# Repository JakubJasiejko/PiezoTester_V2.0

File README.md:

# PiezoTester V2.0

PiezoTester V2.0 is a custom mechatronic test platform for piezoresistive and piezoelectric sensor evaluation under repeatable electromagnetic loading. The project combines an ESP32-based real-time firmware stack, a desktop control application, custom electronics, and mechanical fixtures into one reproducible research toolchain.

It is not just a “demo rig”. It is a full test bench with closed-loop load estimation, sensor-path calibration, adaptive electromagnet characterization, automated reporting, and hardware revision tracking.

## Why This Repository Matters

PiezoTester V2.0 was built to make experimental work faster, cleaner, and more defensible:

- Repeatable cyclic load generation using an electromagnet-driven actuator
- Real-time acquisition of load-cell and piezoresistive sensor data
- Calibration workflows aligned with the actual firmware implementation
- Adaptive PWM-to-load learning for feedforward-assisted ramp tests
- Standard, ramp, and hysteresis test modes
- Desktop export pipeline for CSV and PDF reports
- Versioned PCB and CAD assets kept next to the code that drives them

## Project Structure

```text
PiezoTester_V2.0/
├── firmware/         ESP32 firmware (ESP-IDF, C)
├── desktop_app/      Desktop control and reporting application (Python, PySide6)
├── hardware/
│   ├── PCB/          KiCad projects, board revisions, fabrication outputs
│   └── CAD/          Mechanical CAD parts and assemblies
├── sample_results/   Example CSV/PDF outputs generated by the system
├── docs/             Cross-project documentation, asset sources, image placeholders
├── LICENSE
└── README.md
```

## Core Features

- Multi-mode testing: standard, ramp, and hysteresis acquisition
- One-point load-cell calibration with nominal model correction
- Sensor-path resistance calibration using a reference resistor
- Continuous live mass preview in the calibration workflow
- Advanced electromagnet contact calibration with stored contact-state tables
- Learned PWM-to-load map with point insertion, sorting, interpolation, and reuse
- Feedforward-assisted ramp control with bounded correction steps
- Automatic test summary generation with CSV/PDF export support
- Hardware revision history covering PCB and mechanical development

## Technical Highlights

- Nominal load-cell model based on beam capacity, sensitivity, excitation voltage, and analog gain
- Absolute-value load signal handling to avoid negative mass artifacts
- Resistance reconstruction from divider voltage with a calibration factor stored in NVS
- Electromagnet premodel derived from movement/contact thresholds
- Learned actuator model stored as empirical `(PWM, mass)` pairs
- Piecewise-linear feedforward estimate for ramp tests
- Iterative predictive-corrective update in the ramp controller
- Burst acquisition for hysteresis traces at high sample rate

## Recent Project Wins

- A research-grade calibration flow that mirrors the actual firmware math
- On-device learning of electromagnet behavior instead of fixed lookup-only control
- Integrated desktop reporting that produces presentation-ready PDF summaries
- Multiple PCB revisions with local symbol, footprint, and 3D asset preservation
- A repository structure now being shaped to support publication, fabrication, and onboarding

## Visuals

Add your best visuals here and the repository will immediately look much more “product-level”.

### Hero Shot

_Suggested image: full assembled device on bench, powered on, with the desktop UI visible in the background._

### Desktop Application

_Suggested image: the main control window with charts, statistics, and connection status._

### PCB Render

_Suggested image: 3D render of the latest board revision in KiCad._

### Mechanical Assembly

_Suggested image: CAD assembly or the real fixture with the load cell, electromagnet, and specimen stage._

## Getting Started

### Firmware

See [firmware/README.md](firmware/README.md) for build, flash, and architecture details.

### Desktop Application

See [desktop_app/README.md](desktop_app/README.md) for runtime requirements, launch instructions, and export workflow notes.

### Hardware

See:

- [hardware/README.md](hardware/README.md)
- [hardware/PCB/README.md](hardware/PCB/README.md)
- [hardware/CAD/README.md](hardware/CAD/README.md)

## Asset Sources and Dependencies

The repository intentionally keeps third-party footprint/model provenance visible instead of burying it in tool-generated files.

See:

- [docs/README.md](docs/README.md)
- [docs/THIRD_PARTY_SOURCES.md](docs/THIRD_PARTY_SOURCES.md)

## Sample Outputs

Representative test artifacts are stored in [sample_results/README.md](sample_results/README.md).

## Self-Praise, Because It Is Earned

This project is a serious piece of interdisciplinary work:

- Embedded systems
- measurement engineering
- mechatronic actuation
- hardware design
- desktop tooling
- experimental workflow design

That combination is hard to execute well, and PiezoTester V2.0 already shows a lot more systems thinking than a typical “lab side-project”. It deserves to look the part.

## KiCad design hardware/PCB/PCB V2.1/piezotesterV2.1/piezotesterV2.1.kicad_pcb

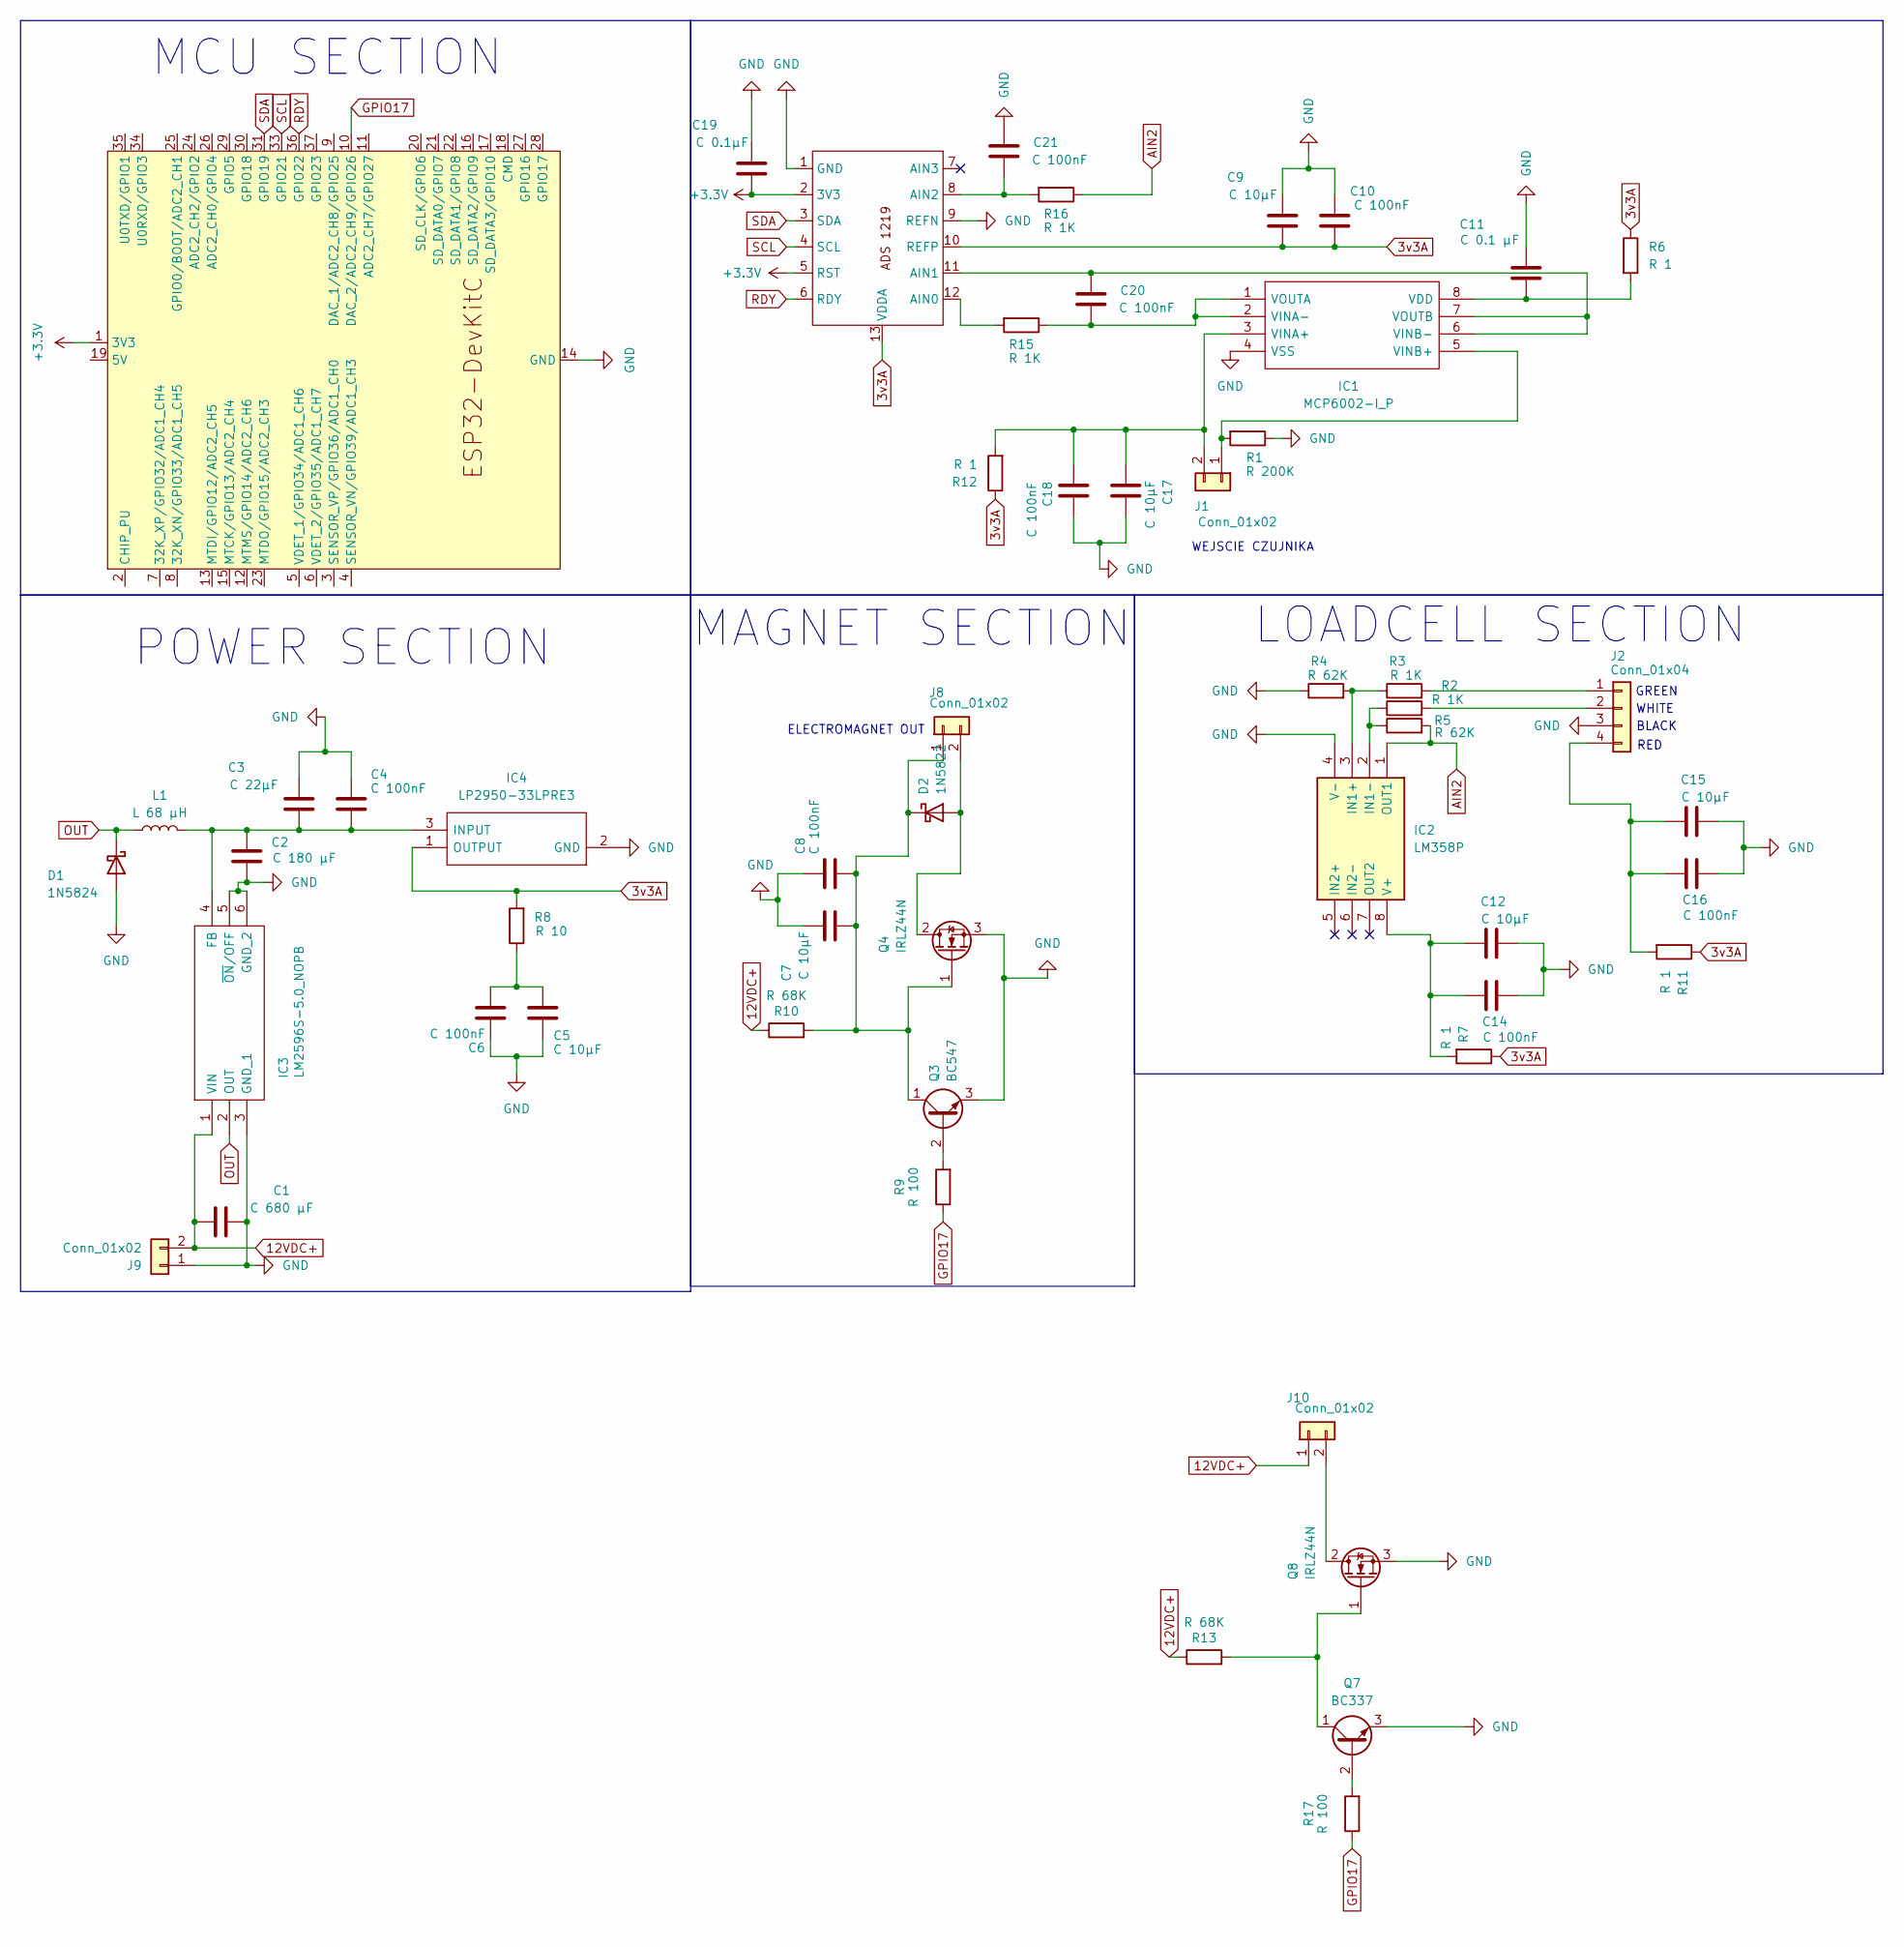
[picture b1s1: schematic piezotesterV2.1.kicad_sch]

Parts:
ADS2: ADS1219
C1: C 680 μF; CP_Radial_D10.0mm_P5.00mm
C2: C 180 μF; CP_Radial_D8.0mm_P3.50mm
C3: C 22μF; C_1206_3216Metric
C4, C6, C8, C10, C14, C16, C18, C20, C21: C 100nF; C_1206_3216Metric
C5, C7, C9, C12, C15, C17: C 10μF; C_1206_3216Metric
C11: C 0.1 μF; C_1206_3216Metric
C19: C 0.1μF; C_1206_3216Metric
D1: 1N5824; D_DO-201AD_P15.24mm_Horizontal
D2: 1N5822; D_DO-201AD_P15.24mm_Horizontal
IC1: MCP6002-I_P; DIP781W56P254L950H533Q8N; Mouser Part Number 579-MCP6002-I/P
IC2: LM358P; DIP781W56P254L950H533Q8N; Mouser Part Number 595-LM358P
IC3: LM2596S-5.0_NOPB; KTT0005B; Mouser Part Number 926-LM2596S-5.0/NOPB
IC4: LP2950-33LPRE3; TL431CLPM; Mouser Part Number 595-LP2950-33LPRE3
J1, J8, J9, J10: Conn_01x02; PinHeader_1x02_P2.54mm_Horizontal
J2: Conn_01x04; PinHeader_1x04_P2.54mm_Horizontal
L1: L 68 μH; L_12x12mm_H6mm
Q3: BC547; TO-92_Inline
Q4, Q8: IRLZ44N; TO-220-3_Vertical
Q7: BC337; TO-92_Inline
R1: R 200K; R_1206_3216Metric
R2, R3, R15, R16: R 1K; R_1206_3216Metric
R4, R5: R 62K; R_1206_3216Metric
R6, R7, R11, R12: R 1; R_1206_3216Metric
R8: R 10; R_1206_3216Metric
R9, R17: R 100; R_1206_3216Metric
R10, R13: R 68K; R_1206_3216Metric
U1: ESP32-DevKitC

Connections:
3v3A: ADS2.10 (REFP), ADS2.13 (VDDA), C9.1, C10.1, IC4.1 (OUTPUT), R6.1, R7.1, R8.2, R11.1, R12.1
12VDC+: C1.1, IC3.1 (VIN), J9.2, J10.1, R10.1, R13.1
+3.3V: ADS2.2 (3V3), ADS2.5 (RST), C19.1, U1.1 (3V3)
AIN2: IC2.1 (OUT1), R5.2, R16.1
GND: ADS2.1 (GND), ADS2.9 (REFN), C1.2, C2.1, C3.2, C4.2, C5.2, C6.2, C7.2, C8.2, C9.2, C10.2, C11.2, C12.2, C14.2, C15.2, C16.2, C17.2, C18.2, C19.2, C21.2, D1.2 (A), IC1.4 (VSS), IC2.4 (V-), IC3.3 (GND_1), IC3.5 (~ON/OFF), IC3.6 (GND_2), IC4.2 (GND), J2.3, J9.1, Q3.3 (E), Q4.3 (S), Q7.3 (E), Q8.3 (S), R1.1, R4.1, U1.14 (GND), U1.32 (GND), U1.38 (GND)
GPIO17: R9.1, R17.1, U1.10 (DAC_2/ADC2_CH9/GPIO26)
unnamed: ADS2.12 (AIN0), R15.2
unnamed: ADS2.11 (AIN1), C20.2, IC1.6 (VINB-), IC1.7 (VOUTB)
unnamed: ADS2.8 (AIN2), C21.1, R16.2
unnamed: C5.1, C6.1, R8.1
unnamed: D2.2 (A), J8.2, Q4.2 (D)
unnamed: C7.1, C8.1, D2.1 (K), J8.1, Q3.1 (C), Q4.1 (G), R10.2
unnamed: C11.1, IC1.8 (VDD), R6.2
unnamed: C17.1, C18.1, IC1.3 (VINA+), J1.2, R12.2
unnamed: C20.1, IC1.1 (VOUTA), IC1.2 (VINA-), R15.1
unnamed: IC1.5 (VINB+), J1.1, R1.2
unnamed: IC2.3 (IN1+), R3.1, R4.2
unnamed: IC2.2 (IN1-), R2.1, R5.1
unnamed: C12.1, C14.1, IC2.8 (V+), R7.2
unnamed: C2.2, C3.1, C4.1, IC3.4 (FB), IC4.3 (INPUT), L1.2
unnamed: J2.1, R3.2
unnamed: J2.2, R2.2
unnamed: C15.1, C16.1, J2.4, R11.2
unnamed: J10.2, Q8.2 (D)
unnamed: Q3.2 (B), R9.2
unnamed: Q7.1 (C), Q8.1 (G), R13.2
unnamed: Q7.2 (B), R17.2
OUT: D1.1 (K), IC3.2 (OUT), L1.1
RDY: ADS2.6 (RDY), U1.36 (GPIO22)
SCL: ADS2.4 (SCL), U1.33 (GPIO21)
SDA: ADS2.3 (SDA), U1.31 (GPIO19)

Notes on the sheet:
ELECTROMAGNET OUT
WHITE
MCU SECTION
BLACK
POWER SECTION
RED
WEJSCIE CZUJNIKA
MAGNET SECTION
GREEN
LOADCELL SECTION

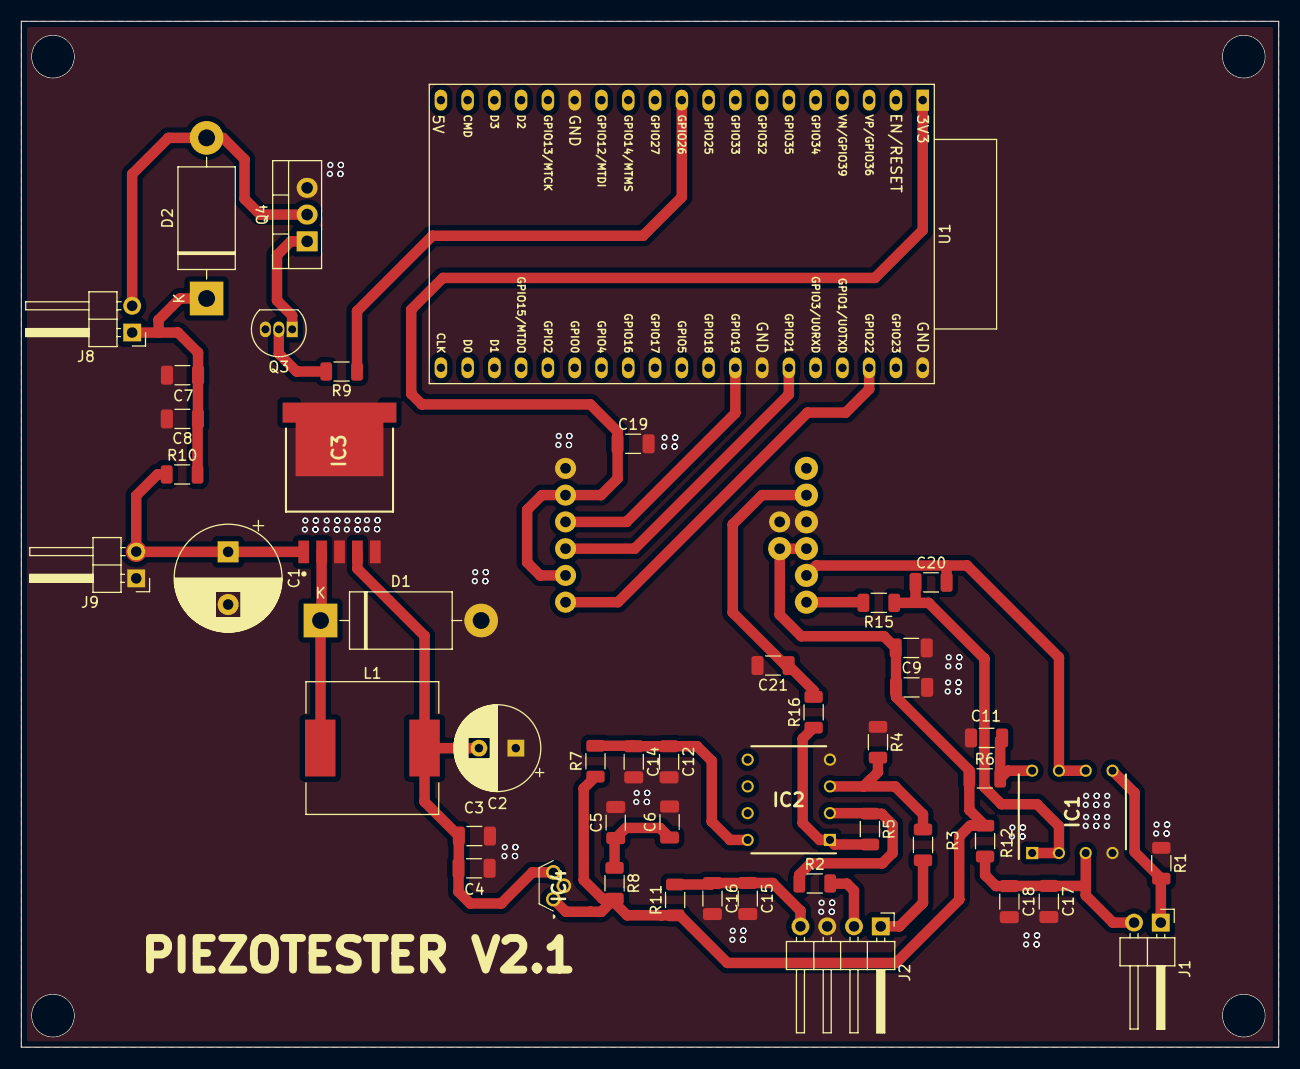
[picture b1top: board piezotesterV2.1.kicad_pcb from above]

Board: 2 copper layers, 119.3 x 97.3 mm, 49 parts (0 on the bottom side), 28 nets.

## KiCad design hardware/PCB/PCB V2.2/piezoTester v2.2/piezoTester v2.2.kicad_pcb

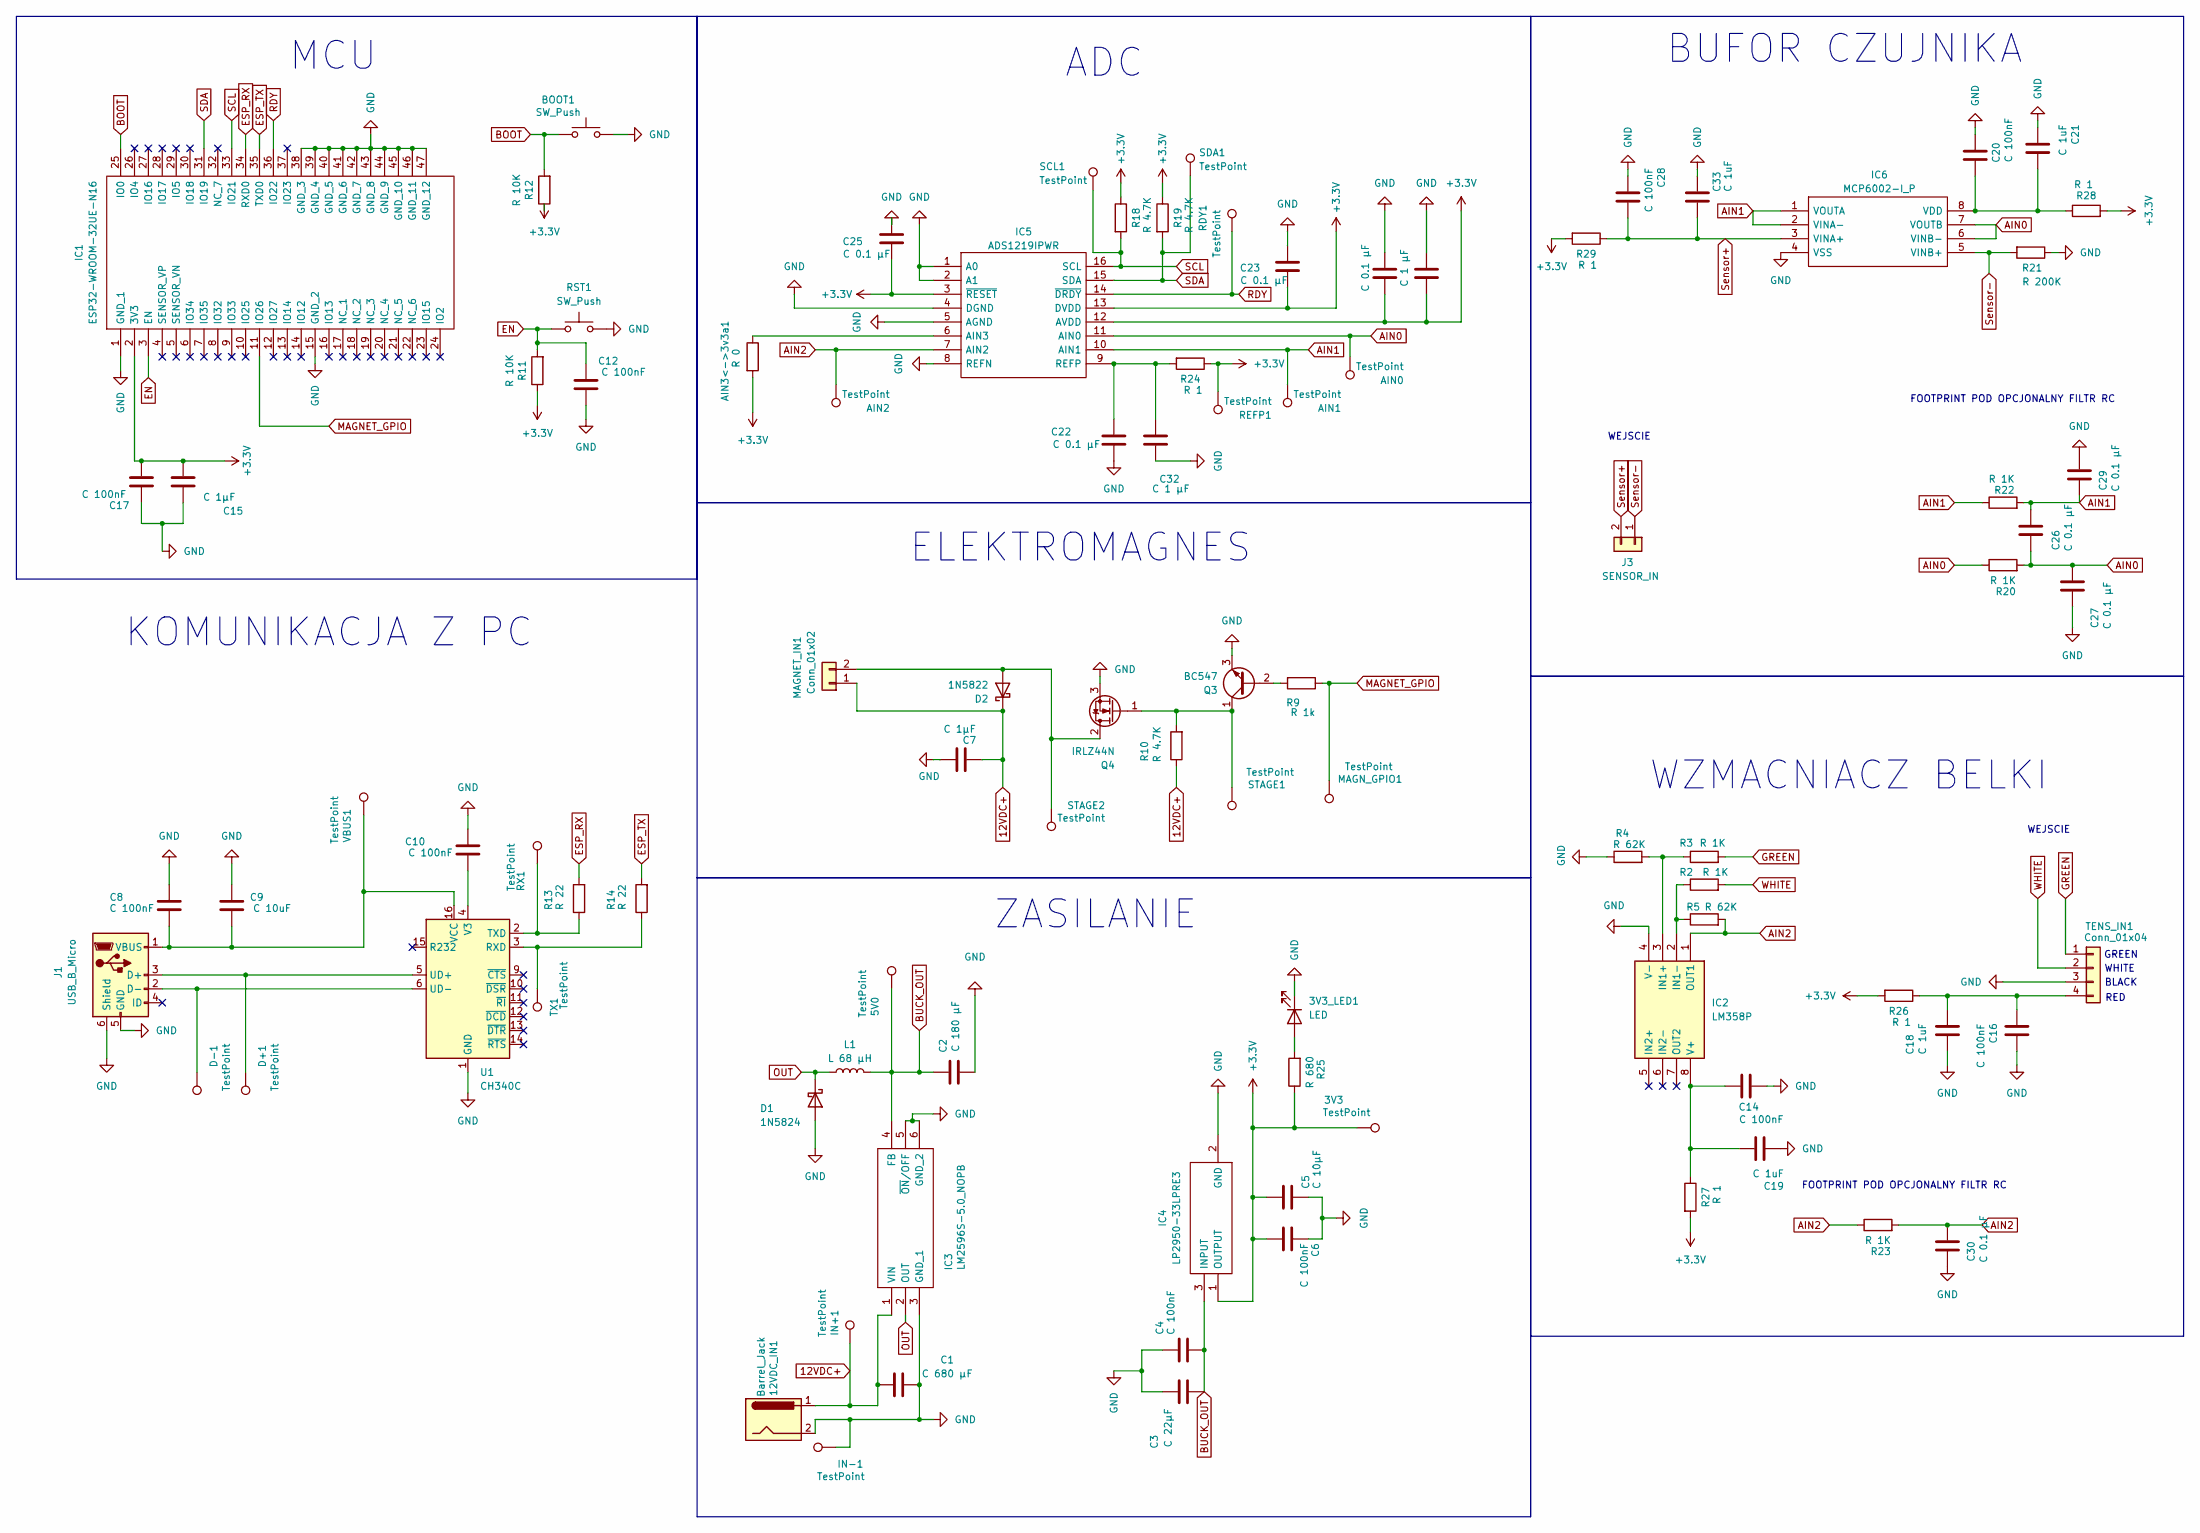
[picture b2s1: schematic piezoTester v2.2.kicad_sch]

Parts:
3V3, 5V0: TestPoint; TestPoint_Pad_D1.0mm
3V3_LED1: LED; LED_1206_3216Metric_Pad1.42x1.75mm_HandSolder
12VDC_IN1: Barrel_Jack; BarrelJack_Wuerth_694108106102_2.5x5.5mm
AIN0, AIN1, AIN2: TestPoint; TestPoint_Pad_D1.0mm
AIN3<->3v3a1: R 0; R_0603_1608Metric_Pad0.98x0.95mm_HandSolder
BOOT1: SW_Push; SW_PUSH_6mm
C1: C 680 μF; CP_Radial_D10.0mm_P5.00mm
C2: C 180 μF; CP_Radial_D8.0mm_P3.50mm
C3: C 22μF; C_1206_3216Metric_Pad1.33x1.80mm_HandSolder
C4, C6, C10, C12, C28: C 100nF; C_1206_3216Metric_Pad1.33x1.80mm_HandSolder
C5: C 10μF; C_1206_3216Metric_Pad1.33x1.80mm_HandSolder
C7: C 1μF; C_1206_3216Metric_Pad1.33x1.80mm_HandSolder
C8, C14, C16, C17, C20: C 100nF; C_0603_1608Metric_Pad1.08x0.95mm_HandSolder
C9: C 10uF; C_0603_1608Metric_Pad1.08x0.95mm_HandSolder
C15: C 1μF; C_0603_1608Metric_Pad1.08x0.95mm_HandSolder
C18, C19, C21: C 1uF; C_0603_1608Metric_Pad1.08x0.95mm_HandSolder
C22, C23, C24, C25, C26: C 0.1 μF; C_0603_1608Metric_Pad1.08x0.95mm_HandSolder
C27, C29, C30: C 0.1 μF; C_1206_3216Metric_Pad1.33x1.80mm_HandSolder
C31, C32: C 1 μF; C_0603_1608Metric_Pad1.08x0.95mm_HandSolder
C33: C 1uF; C_1206_3216Metric_Pad1.33x1.80mm_HandSolder
D1: 1N5824; D_DO-201AD_P15.24mm_Horizontal
D2: 1N5822; D_DO-201AD_P15.24mm_Horizontal
D+1: TestPoint; TestPoint_Pad_D1.0mm
D-1: TestPoint; TestPoint_Pad_D1.0mm
IC1: ESP32-WROOM-32UE-N16; ESP32WROOM32UEN16; Manufacturer_Part_Number ESP32-WROOM-32UE-N16
IC2: LM358P; DIP781W56P254L950H533Q8N; Mouser Part Number 595-LM358P
IC3: LM2596S-5.0_NOPB; KTT0005B; Mouser Part Number 926-LM2596S-5.0/NOPB
IC4: LP2950-33LPRE3; TL431CLPM; Mouser Part Number 595-LP2950-33LPRE3
IC5: ADS1219IPWR; ads1219; Mouser Part Number 595-ADS1219IPWR
IC6: MCP6002-I_P; DIP781W56P254L950H533Q8N; Mouser Part Number 579-MCP6002-I/P
IN+1: TestPoint; TestPoint_Pad_D1.0mm
IN-1: TestPoint; TestPoint_Pad_D1.0mm
J1: USB_B_Micro; USB_Micro-B_Wuerth_629105150521
J3: SENSOR_IN; PinHeader_1x02_P2.54mm_Vertical
L1: L 68 μH; L_12x12mm_H6mm
MAGNET_IN1: Conn_01x02; PinHeader_1x02_P2.54mm_Vertical
MAGN_GPIO1: TestPoint; TestPoint_Pad_D1.0mm
Q3: BC547; TO-92_Inline
Q4: IRLZ44N; TO-220-3_Horizontal_TabDown
R2, R3, R20, R22, R23: R 1K; R_1206_3216Metric_Pad1.30x1.75mm_HandSolder
R4, R5: R 62K; R_1206_3216Metric_Pad1.30x1.75mm_HandSolder
R9: R 1k; R_1206_3216Metric_Pad1.30x1.75mm_HandSolder
R10: R 4.7K; R_1206_3216Metric_Pad1.30x1.75mm_HandSolder
R11, R12: R 10K; R_1206_3216Metric_Pad1.30x1.75mm_HandSolder
R13, R14: R 22; R_1206_3216Metric_Pad1.30x1.75mm_HandSolder
R18, R19: R 4.7K; R_0603_1608Metric_Pad0.98x0.95mm_HandSolder
R21: R 200K; R_1206_3216Metric_Pad1.30x1.75mm_HandSolder
R24: R 1; R_0603_1608Metric_Pad0.98x0.95mm_HandSolder
R25: R 680; R_1206_3216Metric_Pad1.30x1.75mm_HandSolder
R26, R27, R28, R29: R 1; R_1206_3216Metric_Pad1.30x1.75mm_HandSolder
RDY1: TestPoint; TestPoint_Pad_D1.0mm
REFP1: TestPoint; TestPoint_Pad_D1.0mm
RST1: SW_Push; SW_PUSH_6mm
RX1: TestPoint; TestPoint_Pad_D1.0mm
SCL1: TestPoint; TestPoint_Pad_D1.0mm
SDA1: TestPoint; TestPoint_Pad_D1.0mm
STAGE1, STAGE2: TestPoint; TestPoint_Pad_D1.0mm
TENS_IN1: Conn_01x04; PinHeader_1x04_P2.54mm_Vertical
TX1: TestPoint; TestPoint_Pad_D1.0mm
U1: CH340C; SOIC-16_3.9x9.9mm_P1.27mm
VBUS1: TestPoint; TestPoint_Pad_D1.0mm

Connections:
12VDC+: 12VDC_IN1.1, C1.1, C7.2, D2.1 (K), IC3.1 (VIN), IN+1.1, MAGNET_IN1.1, R10.1
+3.3V: 3V3.1, AIN3<->3v3a1.2, C5.1, C6.1, C15.1, C17.1, C23.1, C24.1, C25.1, C31.1, IC1.2 (3V3), IC4.1 (OUTPUT), IC5.3 (~RESET), IC5.12 (AVDD), IC5.13 (DVDD), R11.1, R12.1, R18.1, R19.1, R24.1, R25.1, R26.2, R27.2, R28.2, R29.2, REFP1.1; also elsewhere on the board
AIN0: AIN0.1, C26.2, C27.1, IC5.11 (AIN0), IC6.6 (VINB-), IC6.7 (VOUTB), R20.1, R20.2; also elsewhere on the board
AIN1: AIN1.1, C26.1, C29.2, IC5.10 (AIN1), IC6.1 (VOUTA), IC6.2 (VINA-), R22.1, R22.2; also elsewhere on the board
AIN2: AIN2.1, C30.1, IC2.1 (OUT1), IC5.7 (AIN2), R5.2, R23.1, R23.2; also elsewhere on the board
BOOT: BOOT1.1, IC1.25 (IO0), R12.2; also elsewhere on the board
BUCK_OUT: 5V0.1, C2.2, C3.1, C4.1, IC3.4 (FB), IC4.3 (INPUT), L1.2; also elsewhere on the board
EN: C12.2, IC1.3 (EN), R11.2, RST1.1; also elsewhere on the board
ESP_RX: IC1.34 (RXD0), R13.2; also elsewhere on the board
ESP_TX: IC1.35 (TXD0), R14.2; also elsewhere on the board
GND: 3V3_LED1.1 (K), 12VDC_IN1.2, BOOT1.2, C1.2, C2.1, C3.2, C4.2, C5.2, C6.2, C7.1, C8.2, C9.2, C10.2, C12.1, C14.2, C15.2, C16.2, C17.2, C18.2, C19.2, C20.2, C21.2, C22.1, C23.2, C24.2, C25.2, C27.2, C28.2, C29.1, C30.2, C31.2, C32.1, C33.1, D1.2 (A), IC1.1 (GND_1), IC1.15 (GND_2), IC1.38 (GND_3), IC1.39 (GND_4), IC1.40 (GND_5), IC1.41 (GND_6), IC1.42 (GND_7), IC1.43 (GND_8), IC1.44 (GND_9), IC1.45 (GND_10), IC1.46 (GND_11), IC1.47 (GND_12), IC2.4 (V-), IC3.3 (GND_1), IC3.5 (~ON/OFF), IC3.6 (GND_2), IC3.7, IC3.8, IC4.2 (GND), IC5.1 (A0), IC5.2 (A1), IC5.4 (DGND), IC5.5 (AGND), IC5.8 (REFN), IC6.4 (VSS), IN-1.1, J1.5 (GND), J1.6 (Shield), Q3.3 (E), Q4.3 (S), R4.1, R21.1, RST1.2, TENS_IN1.3, U1.1 (GND); also elsewhere on the board
GREEN: R3.2, TENS_IN1.1
MAGNET_GPIO: IC1.11 (IO26), MAGN_GPIO1.1, R9.1; also elsewhere on the board
unnamed: 3V3_LED1.2 (A), R25.2
unnamed: D2.2 (A), MAGNET_IN1.2, Q4.2 (D), STAGE2.1
unnamed 15: IC2.3 (IN1+), R3.1, R4.2; also elsewhere on the board
unnamed 16: IC2.2 (IN1-), R2.1, R5.1; also elsewhere on the board
unnamed 17: C14.1, C19.1, IC2.8 (V+), R27.1; also elsewhere on the board
unnamed 18: AIN3<->3v3a1.1, IC5.6 (AIN3); also elsewhere on the board
unnamed: C22.2, C32.2, IC5.9 (REFP), R24.2
unnamed 20: C20.1, C21.1, IC6.8 (VDD), R28.1; also elsewhere on the board
unnamed: D+1.1, J1.3 (D+), U1.5 (UD+)
unnamed: D-1.1, J1.2 (D-), U1.6 (UD-)
unnamed: C8.1, C9.1, J1.1 (VBUS), U1.16 (VCC), VBUS1.1
unnamed: Q3.2 (B), R9.2
unnamed: Q3.1 (C), Q4.1 (G), R10.2, STAGE1.1
unnamed: C16.1, C18.1, R26.1, TENS_IN1.4
unnamed: R14.1, TX1.1, U1.3 (RXD)
unnamed: R13.1, RX1.1, U1.2 (TXD)
unnamed: C10.1, U1.4 (V3)
OUT: D1.1 (K), IC3.2 (OUT), L1.1
RDY: IC1.36 (IO22), IC5.14 (~DRDY), RDY1.1; also elsewhere on the board
SCL: IC1.33 (IO21), IC5.16 (SCL), R18.2, SCL1.1; also elsewhere on the board
SDA: IC1.31 (IO19), IC5.15 (SDA), R19.2, SDA1.1; also elsewhere on the board
Sensor+: C28.1, C33.2, IC6.3 (VINA+), J3.2, R29.1; also elsewhere on the board
Sensor-: IC6.5 (VINB+), J3.1, R21.2; also elsewhere on the board
WHITE: R2.2, TENS_IN1.2

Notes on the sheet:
WEJSCIE
FOOTPRINT POD OPCJONALNY FILTR RC
WHITE
BLACK
BUFOR CZUJNIKA
KOMUNIKACJA Z PC
ZASILANIE
RED
MCU
ELEKTROMAGNES
GREEN
ADC
WZMACNIACZ BELKI

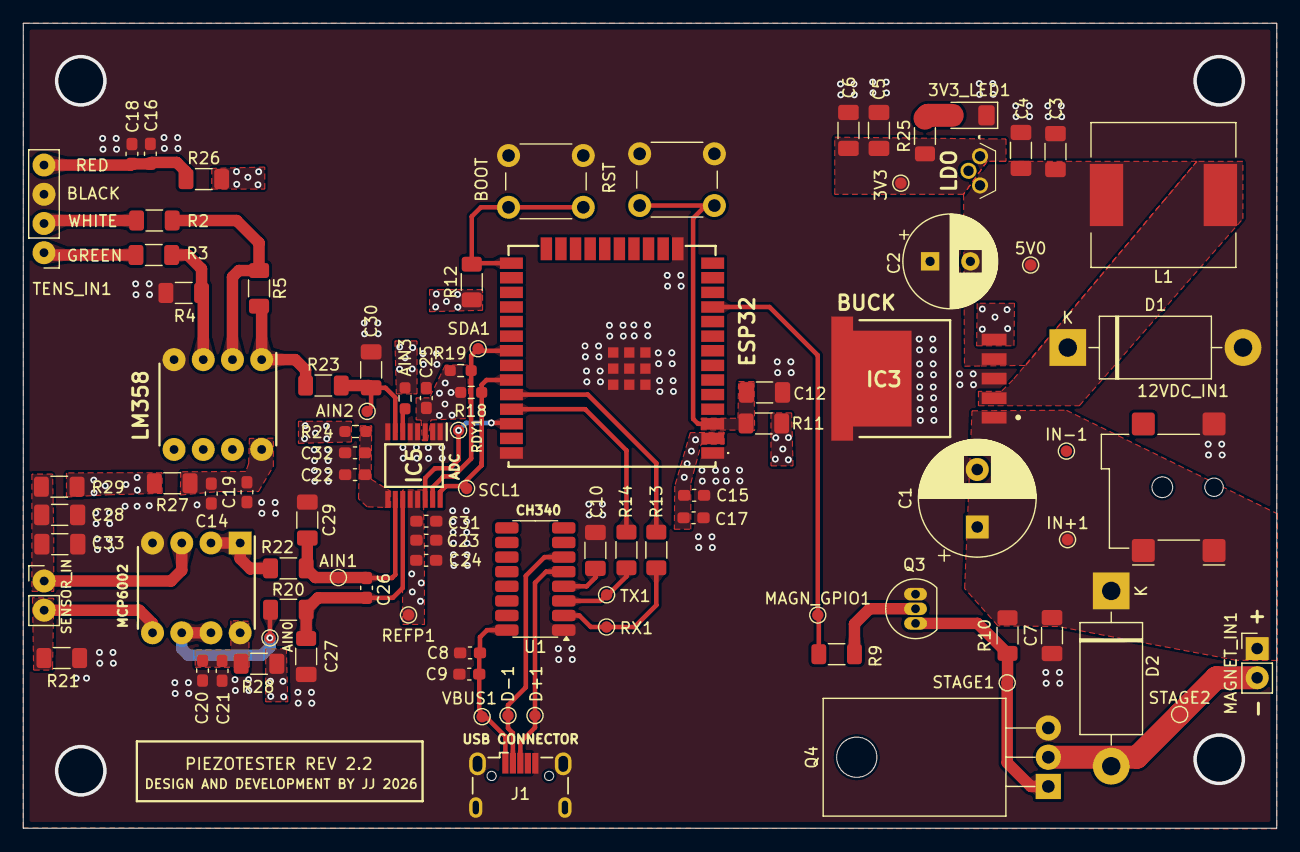
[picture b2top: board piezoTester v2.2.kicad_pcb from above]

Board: 4 copper layers, 109.0 x 70.0 mm, 93 parts (0 on the bottom side), 37 nets.

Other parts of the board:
AIN3: R 0; R_0603_1608Metric_Pad0.98x0.95mm_HandSolder
BOOT: SW_Push; SW_PUSH_6mm
ESP32: ESP32-WROOM-32UE-N16; ESP32WROOM32UEN16
LDO: LP2950-33LPRE3; TL431CLPM
LM358: LM358P; DIP781W56P254L950H533Q8N
MCP6002: MCP6002-I_P; DIP781W56P254L950H533Q8N
RST: SW_Push; SW_PUSH_6mm
SENSOR_IN: SENSOR_IN; PinHeader_1x02_P2.54mm_Vertical

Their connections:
+3.3V: AIN3.2, ESP32.2 (3V3), LDO.1 (OUTPUT); also elsewhere on the board
AIN0: MCP6002.6 (VINB-), MCP6002.7 (VOUTB); also elsewhere on the board
AIN1: MCP6002.1 (VOUTA), MCP6002.2 (VINA-); also elsewhere on the board
AIN2: LM358.1 (OUT1); also elsewhere on the board
BOOT: BOOT.1, ESP32.25 (IO0); also elsewhere on the board
BUCK_OUT: LDO.3 (INPUT); also elsewhere on the board
EN: ESP32.3 (EN), RST.1; also elsewhere on the board
ESP_RX: ESP32.34 (RXD0); also elsewhere on the board
ESP_TX: ESP32.35 (TXD0); also elsewhere on the board
GND: BOOT.2, ESP32.1 (GND_1), ESP32.15 (GND_2), ESP32.38 (GND_3), ESP32.39 (GND_4), ESP32.40 (GND_5), ESP32.41 (GND_6), ESP32.42 (GND_7), ESP32.43 (GND_8), ESP32.44 (GND_9), ESP32.45 (GND_10), ESP32.46 (GND_11), ESP32.47 (GND_12), LDO.2 (GND), LM358.4 (V-), MCP6002.4 (VSS), RST.2; also elsewhere on the board
MAGNET_GPIO: ESP32.11 (IO26); also elsewhere on the board
unnamed 15: LM358.3 (IN1+); also elsewhere on the board
unnamed 16: LM358.2 (IN1-); also elsewhere on the board
unnamed 17: LM358.8 (V+); also elsewhere on the board
unnamed 18: AIN3.1; also elsewhere on the board
unnamed 20: MCP6002.8 (VDD); also elsewhere on the board
RDY: ESP32.36 (IO22); also elsewhere on the board
SCL: ESP32.33 (IO21); also elsewhere on the board
SDA: ESP32.31 (IO19); also elsewhere on the board
Sensor+: MCP6002.3 (VINA+), SENSOR_IN.2; also elsewhere on the board
Sensor-: MCP6002.5 (VINB+), SENSOR_IN.1; also elsewhere on the board

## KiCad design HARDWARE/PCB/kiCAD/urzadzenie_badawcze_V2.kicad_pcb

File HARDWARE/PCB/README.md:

# PCB

This directory stores the electrical design history of PiezoTester V2.0 in KiCad.

## Available Revisions

- `PCB V2.0`
  Early board revision and legacy project assets.
- `PCB V2.1`
  Intermediate revision with local 3D model integration.
- `PCB V2.2`
  Later revision with fabrication outputs and local symbol / footprint libraries.

## What You Will Find Here

- `.kicad_pro`, `.kicad_sch`, `.kicad_pcb` source files
- Local symbol and footprint libraries
- Local 3D models used by KiCad
- Gerber exports and production artifacts
- Revision-specific backup archives generated by KiCad

## Source Provenance

This repository mixes:

- custom project-specific KiCad symbols and footprints
- vendor-derived assets from SamacSys-style libraries
- SparkFun and Espressif-derived reference models for selected modules
- local fixes applied so 3D models resolve directly from the repository

See [../../docs/THIRD_PARTY_SOURCES.md](../../docs/THIRD_PARTY_SOURCES.md) for the documented origin of the main assets.

## Practical Note

KiCad creates autosaves, lock files, cache files, and backups aggressively during active design sessions. The repository now documents these artifacts explicitly and ignores the transient ones where possible, while preserving revision history that is actually useful.

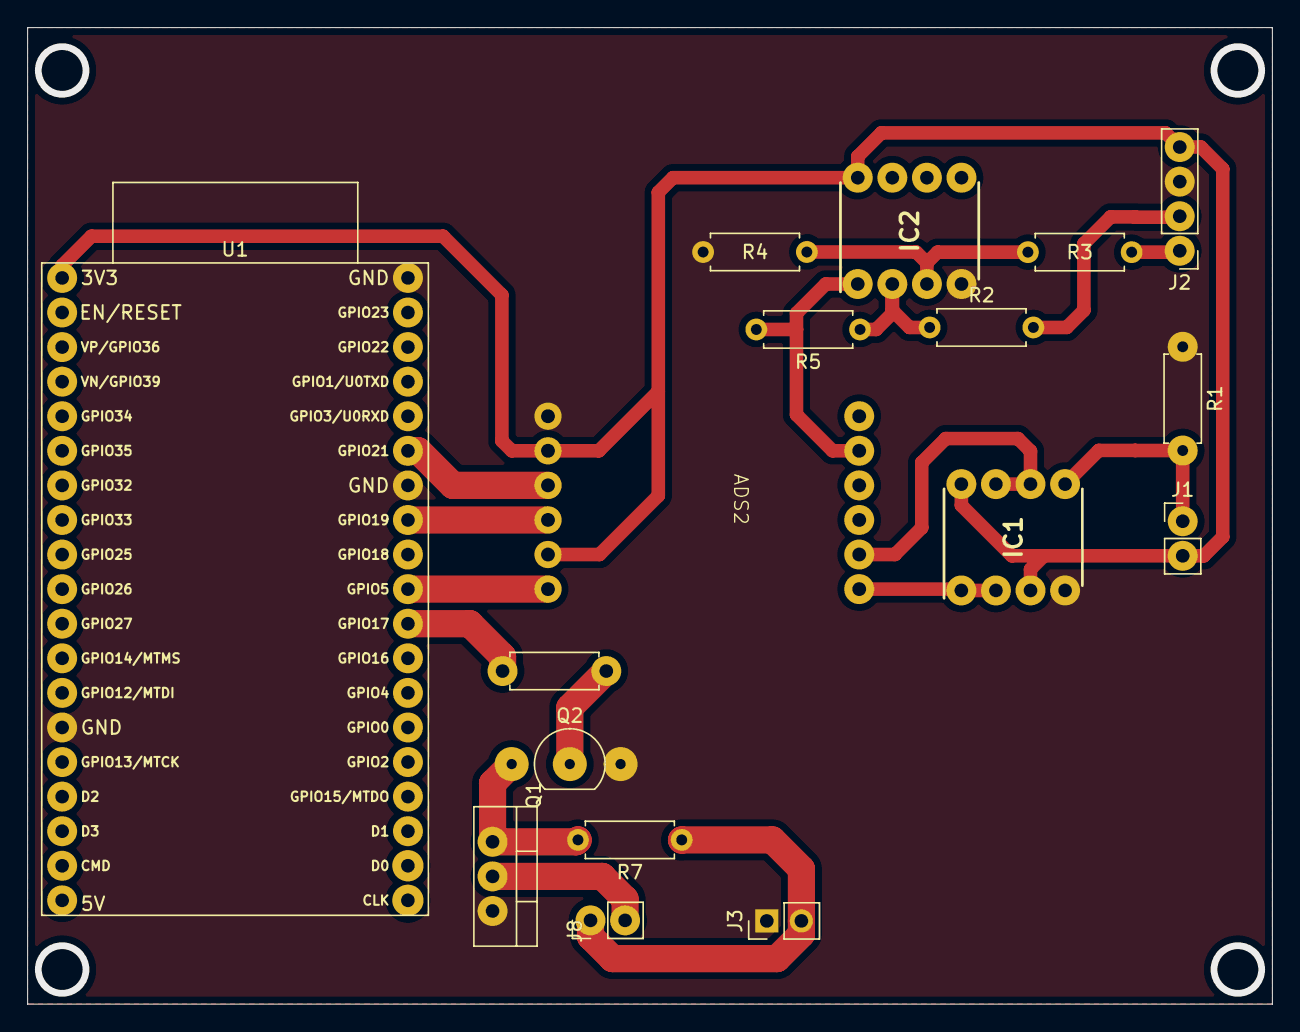
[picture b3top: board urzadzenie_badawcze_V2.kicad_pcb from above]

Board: 2 copper layers, 91.4 x 71.7 mm, 17 parts (0 on the bottom side), 18 nets.

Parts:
ADS2: ADS1219
IC1: MCP6002-I_P; DIP781W56P254L950H533Q8N
IC2: LM358P; DIP781W56P254L950H533Q8N
J1, J3, J8: Conn_01x02; PinHeader_1x02_P2.54mm_Vertical
J2: Conn_01x04; PinHeader_1x04_P2.54mm_Vertical
Q1: IRLZ44N; TO-220-3_Vertical
Q2: BC547; TO-92_Inline
R1: R 200K; R_Axial_DIN0207_L6.3mm_D2.5mm_P7.62mm_Horizontal
R2, R3: R 1K; R_Axial_DIN0207_L6.3mm_D2.5mm_P7.62mm_Horizontal
R4, R5: R 62K; R_Axial_DIN0207_L6.3mm_D2.5mm_P7.62mm_Horizontal
R6: R 100; R_Axial_DIN0207_L6.3mm_D2.5mm_P7.62mm_Horizontal
R7: R 68K; R_Axial_DIN0207_L6.3mm_D2.5mm_P7.62mm_Horizontal
U1: ESP32-DevKitC

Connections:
+3.3V: ADS2.2 (3V3), ADS2.5 (RST), IC1.3 (VINA+), IC1.8 (VDD), IC2.8 (V+), J1.2, J2.4, U1.1 (3V3)
GND: ADS2.1 (GND), IC1.4 (VSS), IC2.4 (V-), J2.3, J3.1, Q1.3 (S), Q2.3 (E), R1.1, R4.1, U1.14 (GND), U1.32 (GND), U1.38 (GND)
GPIO17: R6.1, U1.28 (GPIO17)
unnamed: ADS2.12 (AIN0), IC1.1 (VOUTA), IC1.2 (VINA-)
unnamed: ADS2.11 (AIN1), IC1.6 (VINB-), IC1.7 (VOUTB)
unnamed: ADS2.8 (AIN2), IC2.1 (OUT1), R5.2
unnamed: IC1.5 (VINB+), J1.1, R1.2
unnamed: IC2.3 (IN1+), R3.1, R4.2
unnamed: IC2.2 (IN1-), R2.1, R5.1
unnamed: J2.1, R3.2
unnamed: J2.2, R2.2
unnamed: J3.2, J8.1, R7.1
unnamed: J8.2, Q1.2 (D)
unnamed: Q1.1 (G), Q2.1 (C), R7.2
unnamed: Q2.2 (B), R6.2
RDY: ADS2.6 (RDY), U1.29 (GPIO5)
SCL: ADS2.4 (SCL), U1.31 (GPIO19)
SDA: ADS2.3 (SDA), U1.33 (GPIO21)

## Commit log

2025-11-10 Added Matlab and PCB V2.1 completed fw
2026-03-14 PCB v2.2
2026-04-17 feat: add nominal load-cell calibration flow
2026-04-17 fix: auto-start live preview and harden pdf export
2026-04-18 feat: add ramp test mode with pwm learning
2026-04-18 feat: add electromagnet premodel controls
2026-04-18 feat: split electromagnet movement and contact thresholds
2026-04-18 feat: add advanced electromagnet calibration tools
2026-04-18 fix: suspend live preview during zero calibration
2026-04-18 refactor: simplify calibration flow and speed preview
2026-04-18 fix: stabilize calibration dialog startup
2026-04-18 fix: avoid GUI updates from calibration worker threads
2026-04-18 fix: open summary dialog after automatic test completion
2026-04-18 feat: add point-by-point electromagnet contact calibration table
2026-04-18 feat: persist electromagnet contact calibration points
2026-04-18 refactor: make contact calibration grid configurable
2026-04-18 ux: prefer ttyUSB ports in selector
2026-04-18 fix: preserve selected contact state during config sync
2026-04-18 fix: enlarge firmware response buffer for status payload
2026-04-18 feat: add hysteresis test mode and reporting
2026-04-18 feat: implement cycle-based hysteresis reporting
2026-04-18 fix: redefine hysteresis as repeated load-unload cycles
2026-04-18 feat: add 10s pause between non-hysteresis samples
2026-04-18 fix: retry stalled test reads and keep partial summary
2026-04-18 fix: return test done after final sample
2026-04-18 feat: prefill ramp range from learned electromagnet model
2026-04-19 docs: polish repo structure and documentation
2026-04-19 chore: sync repository with current workspace layout
